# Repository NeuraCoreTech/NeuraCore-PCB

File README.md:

# FPGA Dev Board - Xilinx XC7Z020

Custom Zynq-7000 FPGA + ARM SoC development board based on the Xilinx XC7Z020-1CLG484I.

This repository contains the PCB design files, schematics, BOM, and hardware documentation for the board.

---

## Overview

This board is designed as a general-purpose Zynq development platform featuring:

- Xilinx XC7Z020 SoC
- DDR3L memory subsystem
- Gigabit Ethernet
- USB programming and UART interface
- USB OTG support
- QSPI boot flash
- Multi-rail power architecture
- FPGA PL expansion banks

The design targets embedded Linux, FPGA acceleration, digital design experimentation, and hardware/software co-design workflows.

---

## Hardware Features

### Processing System
- Xilinx XC7Z020-1CLG484I
- Dual-core ARM Cortex-A9
- FPGA programmable logic fabric

### Memory
- DDR3L memory interface
- Fly-by routed DDR topology
- Dedicated VTT termination rail

### Power Architecture
Power rails:
- 5V Input
- 3.3V
- 1.8V
- 1.35V
- 1.0V
- 0.675V DDR termination

Power sequencing implemented using:
- TPS56628 buck converters
- Dedicated PG sequencing
- Protection and filtering stages

### Connectivity
- Gigabit Ethernet (RTL8211F PHY)
- USB-C programming interface
- USB OTG via USB3320 ULPI PHY
- FT2232H for JTAG + UART

### Boot & Programming
- QSPI flash boot support
- Boot mode DIP switches
- Digilent HS3 compatible JTAG header

### FPGA I/O
- PL banks exposed for expansion
- HDMI-capable bank preparation
- Mixed-voltage IO support

---

## Repository Structure

```text
.
├── schematic/
├── pcb/
├── bom/
├── manufacturing/
├── images/
└── README.md
```

---

## Design Files

| File | Description |
|------|-------------|
| Schematic PDF | Complete board schematic |
| BOM | Bill of materials |
| PCB Layout | Board routing and placement |
| Gerbers | Manufacturing outputs |

---

## Key Components

| Component | Part |
|-----------|------|
| SoC | XC7Z020-1CLG484I |
| DDR3L | MT41K256M16TW |
| Ethernet PHY | RTL8211F-CG |
| USB PHY | USB3320 |
| USB/JTAG Interface | FT2232HL |
| QSPI Flash | W25Q512JVEIQ |

---

## Development Status

Current revision:
- v0.07

Status:
- Hardware prototype
- Under validation/testing

Known improvements and future revisions are documented within the schematic notes.

---

## Toolchain

Designed using:
- EasyEDA

Firmware/software targets:
- Vivado
- Vitis
- PetaLinux

---

## Bring-Up Checklist

- [ ] Verify all power rails
- [ ] Validate power sequencing
- [ ] DDR memory calibration
- [ ] QSPI boot validation
- [ ] JTAG connectivity test
- [ ] Ethernet PHY validation
- [ ] USB OTG validation

---

## Manufacturing Notes

Before fabrication:
- Verify impedance-controlled traces
- Review DDR length matching
- Validate power plane integrity
- Confirm connector footprints
- Review DFM constraints

---

## Contributors

- Krishna H. Patil
- Mohit Singh 
- Prajwal
- Arnav Yadnopavit

---
## Acknowledgements

This part of project (PCB) is heavily based on the open-source Zynq-7000 FPGA development board work by rehsd.

Original reference project:
https://github.com/rehsd/FPGA

Additional documentation and development notes:
https://www.rehsdonline.com/

The hardware architecture, schematic structure, and several subsystem implementations were adapted from the original project and modified for NeuraCoreTech requirements.

We thank rehsd for openly publishing the design resources and documentation.

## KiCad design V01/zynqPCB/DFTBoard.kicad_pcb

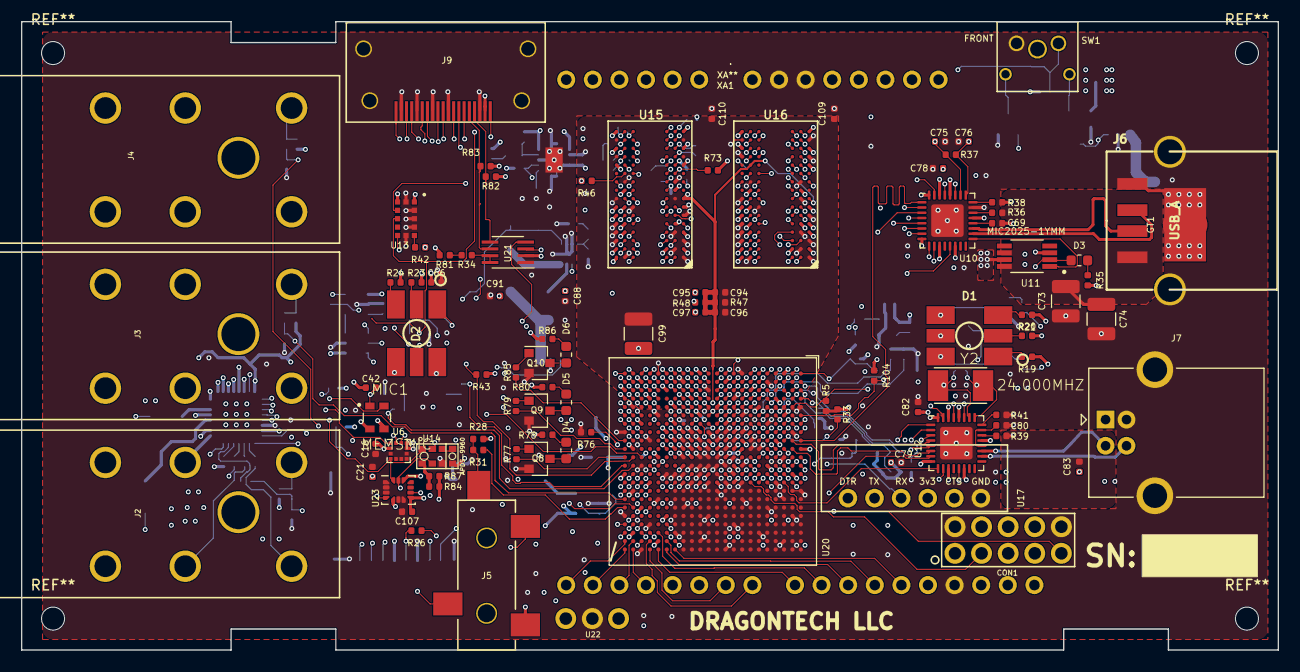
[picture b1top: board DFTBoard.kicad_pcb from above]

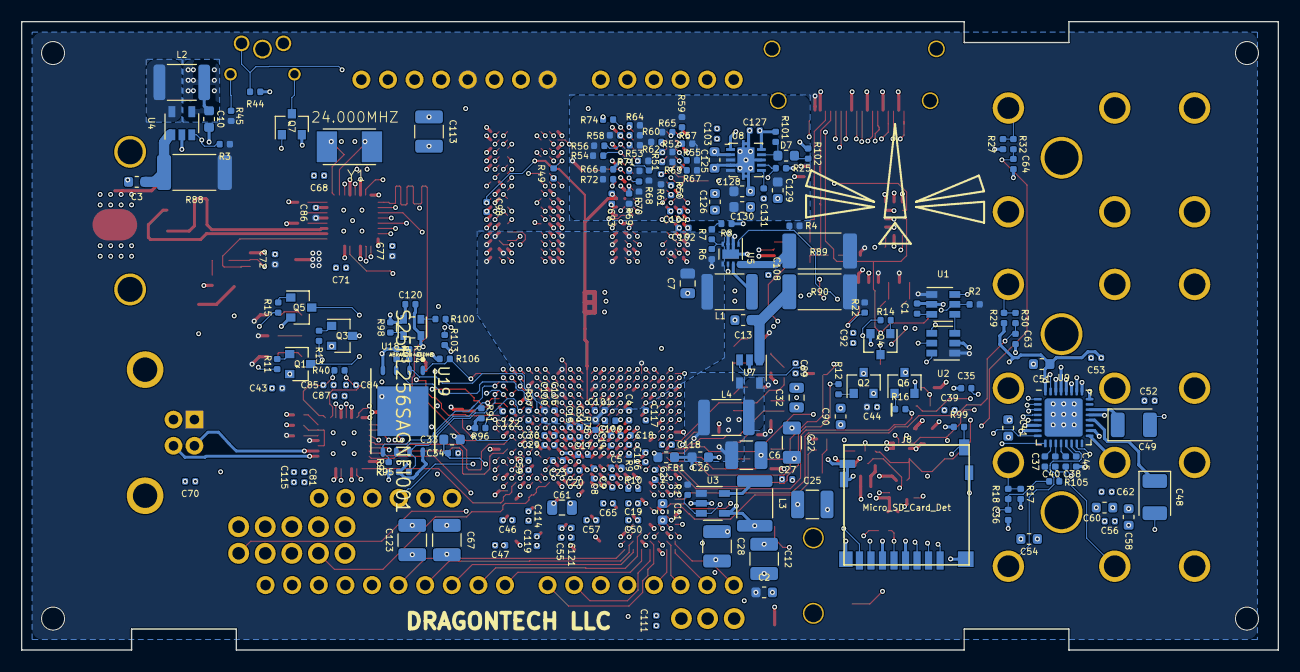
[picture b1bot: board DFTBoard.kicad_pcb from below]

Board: 8 copper layers, 120.0 x 60.0 mm, 295 parts (200 on the bottom side), 302 nets.

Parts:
C1, C4, C8, C14, C15, C17, C18, C23, C29, C30, C31, C34, C46, C47, C50, C55, C65, C78, C87, C101, C102, C103, C104, C108, C116, C117, C118, C119, C121: .47uF; C_0402_1005Metric
C2, C3, C10, C11, C13, C26, C33, C41, C51, C54, C58, C60, C90, C125, C126, C128, C129, C130: 10uF; C_0603_1608Metric
C5, C9, C19, C20, C21, C24, C27, C42, C57, C59, C66, C83, C89, C100, C114, C115, C122, C127: 4.7uF; C_0402_1005Metric
C6, C12, C25, C28, C67, C73, C74, C99, C123: 100uF; C_1210_3225Metric
C7, C32, C61: 47uF; C_0805_2012Metric
C16, C36, C39, C52, C53, C56, C62, C63, C64, C68, C70, C71, C72, C77, C79, C81, C82, C86, C88, C94, C95, C96, C97, C107, C131: .1uF; C_0402_1005Metric
C22: 330uF; C_1206_3216Metric
C35, C69, C80: 2.2uF; C_0402_1005Metric
C37, C38, C40, C43, C44, C45, C91, C92: 1uF; C_0402_1005Metric
C48, C49: 220uF Tant.; CP_EIA-3528-12_Kemet-T
C75, C76, C84, C85: 18pF; C_0402_1005Metric
C93, C98, C105, C106, C109, C110, C111, C120: .01uF; C_0402_1005Metric
C113: 47uF; C_1210_3225Metric
CON1: AVR-JTAG-10; XilinxJTAG
D1, D2: LED_RGB; PLCC6-SM-RGB-LED
D3, D4, D5, D6, D7: BLUE LED; C_0603_1608Metric
FB1: 120R, 100 MHz, size 0603; C_0603_1608Metric
GT1: GNDTIE; gndtie
J2, J3, J4: AUDIO JACK; RA49C14B
J5: JACK_TRS_4PINS; SJ-352X-SMT
J6: USB_A; USB-A-Receptacle-FCI_87583
J7: USB_B; USB_B_OST_USB-B1HSxx_Horizontal
J8: Micro_SD_Card_Det; AMPHENOL-114-00841-68
J9: HDMI_A; 10029449-111RLF
L1, L2, L3, L4: 2.2uH; C_1812_4532Metric
MIC1: MEMSMIC; MIC_SPW2430HR5H-B
Q1, Q2, Q3, Q4, Q5, Q6, Q7, Q8, Q9, Q10: IRLML2502; SOT-23
R1, R2, R3, R4, R5, R17, R27, R28, R29, R34, R81, R101: 100k; R_0402_1005Metric
R6, R33, R36, R39, R42, R43, R44: 10k; R_0402_1005Metric
R7, R46, R49: 240 1%; R_0402_1005Metric
R8, R9, R10, R74, R82, R83, R98, R103, R104: 4.7k; R_0402_1005Metric
R11, R12, R13, R14, R15, R16, R19, R20, R22, R23: 100; R_0402_1005Metric
R18, R30, R31, R32: 49.9k; R_0402_1005Metric
R21, R24, R35, R45, R78, R80, R86, R102: 150; R_0402_1005Metric
R25, R91, R92, R93, R94, R95, R96, R97, R106: 20k; R_0402_1005Metric
R26, R84, R87: 47; R_0402_1005Metric
R37, R40: 1M; R_0402_1005Metric
R38, R41: 8.06k 1%; R_0402_1005Metric
R47, R48: 10k 1%; R_0402_1005Metric
R50, R75, R76: 80.6 1%; R_0402_1005Metric
R51, R52, R53, R54, R55, R56, R57, R58, R59, R60, R61, R62, R63, R64, R65, R66, R67, R68, R69, R70, R71, R72, R73: 40.2 1%; R_0402_1005Metric
R77, R79, R85, R105: 1k; R_0402_1005Metric
R88, R89, R90: .05; R_2512_6332Metric
R99: 47k; R_0402_1005Metric
R100: 24.9 1%; R_0402_1005Metric
SW1: TL6215RF200BDT; tl6215_right_angle
U1, U2: LM3880; SOT-23-6
U3: SC189 - 1.0V; SOT-23-5
U4: SC189 - 3.3V; SOT-23-5
U5: TLV62080DSGx; WSON-8-1EP_2x2mm_P0.5mm_EP0.9x1.6mm
U6: LIS2HH12; LGA-12_2x2mm_P0.5mm
U7: SC189 - 1.8V; SOT-23-5
U8: TPS51200DRCR; VSON-10-1EP_3x3mm_P0.5mm_EP1.65x2.4mm_ThermalVias
U9: TLV320AIC3104; QFN-32-1EP_5x5mm_P0.5mm_EP3.65x3.65mm
U10, U12: USB3320; QFN-32-1EP_5x5mm_P0.5mm_EP3.1x3.1mm
U11: MIC2025-1YMM; SOP65P490X110-8N
U13: VL53L1CXV0FY/1; Optical_LGA12
U14: APDS-9960; APDS_9960
U15, U16: MT41K256M16HA-125_E; FBGA-96-DDR3-SDRAM
U17: FTDITypeUART; FTDI_CONN
U18: ABRACON-ASDMB; XTAL_ASDMB-24.000MHZ-LC-T
U19: S25FL256SAGNFI001; Cypress-002-18827-0-0-0
U20: xc7z020clg484; BGA-484_19.0x19.0mm_Layout22x22_P0.80mm_dia0.40mm
U21: PCA9306; SSOP-8_2.95x2.8mm_P0.65mm
U22: TSOP344; JUMPER_3PIN
U23: LSM6DSLTR; LGA-14_3x2.5mm_P0.5mm_LayoutBorder3x4y
XA1: Arduino_Uno_Shield_Simplified
Y1, Y2: 24.000MHZ; XTAL500X320X130N

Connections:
1v0en: R1.2, U1.6, U3.3
1v8en: R2.2, U1.5, U7.3
1v35PG: U5.6, U20.V4
1v35en: R4.2, U2.5, U5.1
3v3en: R3.2, U2.6, U4.3
+1V0: C8.1, C9.1, C11.1, C12.1, C23.1, C24.1, C25.1, C27.1, C28.1, C29.1, C30.1, C31.1, L3.2, U3.4, U20.G8, U20.H9, U20.H11, U20.J8, U20.J10, U20.J12, U20.J14, U20.K13, U20.L8, U20.L14, U20.M13, U20.N8, U20.N14, U20.P13, U20.R8, U20.R14
+1V8: C4.1, C5.1, C6.1, C14.1, C15.1, C17.1, C18.1, C19.1, C20.1, C22.1, C26.1, C32.1, C51.1, C53.1, C78.1, C87.1, CON1.4, FB1.2, L4.2, R9.2, R10.2, R17.1, R27.2, R28.2, R29.2, R44.1, U7.4, U9.32, U10.28, U10.30, U12.28, U12.30, U20.H10, U20.K9, U20.K11, U20.M9, U20.P9, U20.R12, U20.T7, U20.T8, U20.T9, U20.T10
+1V35: C7.1, C94.1, C96.1, C99.1, C100.1, C101.1, C102.1, C103.1, C104.1, C109.1, C110.1, C125.1, C126.1, L1.2, R6.2, R47.1, R75.2, U5.5, U8.2, U15.A1, U15.A8, U15.B2, U15.C1, U15.C9, U15.D2, U15.D9, U15.E9, U15.F1, U15.G7, U15.H2, U15.H9, U15.K2, U15.K8, U15.N1, U15.N9, U15.R1, U15.R9, U16.A1, U16.A8, U16.B2, U16.C1, U16.C9, U16.D2, U16.D9, U16.E9, U16.F1, U16.G7, U16.H2, U16.H9, U16.K2, U16.K8, U16.N1, U16.N9, U16.R1, U16.R9, U20.E2, U20.F5, U20.H1, U20.J4, U20.K7, U20.M3, U20.N6, U20.R2, U20.V1
+3V3: C10.1, C16.1, C21.1, C39.2, C41.2, C46.1, C47.1, C50.1, C52.2, C54.2, C55.1, C56.2, C57.1, C58.2, C59.1, C60.1, C61.1, C62.1, C65.1, C66.1, C67.1, C68.1, C70.1, C71.1, C79.1, C81.1, C82.1, C88.1, C89.1, C90.2, C91.2, C92.2, C107.1, C111.1, C113.1, C114.1, C115.1, C116.1, C117.1, C118.1, C119.1, C120.1, C121.1, C122.1, C123.1, C127.2, J8.4, L2.2, R5.1, R25.1, R33.2, R35.2, R42.1, R43.1, R82.1, R83.1, R84.2, R87.1, R95.2, R98.2, R99.1, R101.1, R102.2, R103.1, R104.1, R106.2, U4.4, U6.2, U6.9, U6.10, U8.10, U9.7, U9.18, U9.24, U9.25, U10.8, U10.11, U10.14, U10.32, U12.8, U12.11, U12.14, U12.32, U13.1, U13.11, U14.5, U17.3, U18.4, U19.8, U20.A10, U20.AA10, U20.AA20, U20.AB3, U20.AB13, U20.B3, U20.B13, U20.C6, U20.D9, U20.E12, U20.T5, U20.U8, U20.U18, U20.V11, U20.V21, U20.W4, U20.W14, U20.Y7, U20.Y17, U21.2, U22.3, U23.5, U23.8, U23.12, XA1.3V3, XA1.IORF
+5V: C2.1, C43.1, C44.1, C72.1, C77.1, C83.2, C86.1, J7.1, J9.18, R1.1, R2.1, R3.1, R4.1, R19.1, R20.1, R21.1, R22.1, R23.1, R24.1, R39.2, R45.1, R78.1, R80.2, R81.2, R86.2, R88.1, R89.1, R90.1, U1.1, U2.1, U3.1, U10.21, U11.7, U12.21, XA1.5V1, XA1.VIN
/Audio/HPRCOM_C_N: C48.2, J5.3
/Audio/HPRCOM_C_P: C49.2, J5.2
/Audio/HPSWITCH: J5.4, R28.1, R31.2
/Audio/INSWITCH: J2.TB, R17.2, R18.2
/Audio/JACK_INC_N: C40.1, U9.11
/Audio/JACK_INC_P: C37.1, U9.10
/Audio/JACK_IN_N: C40.2, J2.R
/Audio/JACK_IN_P: C37.2, J2.T
/Audio/LED_1BA: D1.3, R21.2
/Audio/LED_1BC: D1.4, Q5.3
/Audio/LED_1GA: D1.2, R20.2
/Audio/LED_1GC: D1.5, Q3.3
/Audio/LED_1RA: D1.1, R19.2
/Audio/LED_1RC: D1.6, Q1.3
/Audio/LED_2BA: D2.3, R24.2
/Audio/LED_2BC: D2.4, Q6.3
/Audio/LED_2GA: D2.2, R23.2
/Audio/LED_2GC: D2.5, Q4.3
/Audio/LED_2RA: D2.1, R22.2
/Audio/LED_2RC: D2.6, Q2.3
/Audio/LSWITCH: J3.TB, R29.1, R30.2
/Audio/MICBIAS: C35.2, C42.1, MIC1.1, U9.15
/Audio/RSWITCH: J4.TB, R27.1, R32.2
/Audio/SIGC_F: C38.2, MIC1.4
/Audio/SIG_F: C38.1, U9.12
/DDR3/PGOOD_LED: D7.2, R102.1
/DDR3/VREF: C93.1, C94.2, C95.1, C96.2, C97.1, C98.1, C105.1, C106.1, R47.2, R48.1, U8.1, U15.H1, U15.M8, U16.H1, U16.M8, U20.H7, U20.P7
/DDR3/ZQH: R46.1, U15.L8
/DDR3/ZQL: R49.1, U16.L8
/LCD50/SLED0_D: D4.1, Q8.3
/LCD50/SLED0_G: Q8.1, R77.1
/LCD50/SLED0_R: D4.2, R78.2
/LCD50/SLED1_D: D5.1, Q9.3
/LCD50/SLED1_G: Q9.1, R79.1
/LCD50/SLED1_R: D5.2, R80.1
/LCD50/SLED2_D: D6.1, Q10.3
/LCD50/SLED2_G: Q10.1, R85.1
/LCD50/SLED2_R: D6.2, R86.1
/Power/1V0TOLX: L3.1, U3.5
/Power/1V8TOLX: L4.1, U7.5
/Power/1V8_CS: C13.1, R90.2, U7.1
/Power/1V35_CS: C108.1, R89.2, U5.8
/Power/3V3TOLX: L2.1, U4.5
/Power/3V3_CS: C3.1, R88.2, U4.1
/Power/VCCAUX: C33.1, C34.1, FB1.1, U20.L10, U20.N10, U20.P11, U20.R10
/Sensors/3.3V_R: R84.1, R87.2, U14.8
/Sensors/TEMPO_LED_D: Q7.3, SW1.3
/Sensors/TEMPO_LED_R: R45.2, SW1.4
/USB/USBH_FLAG_LED: D3.2, R35.1
ACC_INT1: U6.12, U20.W12
ACC_INT2: U6.11, U20.V12
AX_TCLK: CON1.1, U20.G11
AX_TDI: CON1.9, U20.H13
AX_TDO: CON1.3, U20.G14
AX_TMS: CON1.5, U20.G12
BOOTSPI_CS: R106.1, U19.1, U20.A1
BOOTSPI_DQ0_BMODE3: R92.1, U19.5, U20.A2
BOOTSPI_DQ1_BMODE1: R94.1, U19.2, U20.F6
BOOTSPI_DQ2_BMODE2: R93.1, U19.3, U20.E4
BOOTSPI_DQ3_BMODE0: R95.1, U19.7, U20.A3
BOOTSPI_SCK_BMODE4: R91.1, U19.6, U20.A4
CLK33.33: R100.2, U18.3
DDR3_A0: R51.1, U15.N3, U16.N3, U20.M4
DDR3_A1: R52.1, U15.P7, U16.P7, U20.M5
DDR3_A2: R53.1, U15.P3, U16.P3, U20.K4
DDR3_A3: R54.1, U15.N2, U16.N2, U20.L4
DDR3_A4: R55.1, U15.P8, U16.P8, U20.K6
DDR3_A5: R56.1, U15.P2, U16.P2, U20.K5
DDR3_A6: R57.1, U15.R8, U16.R8, U20.J7
DDR3_A7: R58.1, U15.R2, U16.R2, U20.J6
DDR3_A8: R59.1, U15.T8, U16.T8, U20.J5
DDR3_A9: R60.1, U15.R3, U16.R3, U20.H5
DDR3_A10: R61.1, U15.L7, U16.L7, U20.J3
DDR3_A11: R62.1, U15.R7, U16.R7, U20.G5
DDR3_A12: R63.1, U15.N7, U16.N7, U20.H4
DDR3_A13: R64.1, U15.T3, U16.T3, U20.F4
DDR3_A14: R65.1, U15.T7, U16.T7, U20.G4
DDR3_BA0: R66.1, U15.M2, U16.M2, U20.L7
DDR3_BA1: R67.1, U15.N8, U16.N8, U20.L6
DDR3_BA2: R68.1, U15.M3, U16.M3, U20.M6
DDR3_CAS#: R70.1, U15.K3, U16.K3, U20.P3
DDR3_CKE: U15.K9, U16.K9, U20.V3
DDR3_CK_N: R50.2, U15.K7, U16.K7, U20.N5
DDR3_CK_P: R50.1, U15.J7, U16.J7, U20.N4
DDR3_CS#: R73.1, U15.L2, U16.L2, U20.P6
DDR3_DM0: U16.E7, U20.B1
DDR3_DM1: U16.D3, U20.H3
DDR3_DM2: U15.E7, U20.P1
DDR3_DM3: U15.D3, U20.AA2
DDR3_DQ0: U16.E3, U20.C3
DDR3_DQ1: U16.F7, U20.F2
DDR3_DQ2: U16.F2, U20.B2
DDR3_DQ3: U16.F8, U20.F1
DDR3_DQ4: U16.H3, U20.E3
DDR3_DQ5: U16.H8, U20.E1
DDR3_DQ6: U16.G2, U20.D3
DDR3_DQ7: U16.H7, U20.D1
DDR3_DQ8: U16.D7, U20.L3
DDR3_DQ9: U16.C3, U20.L1
DDR3_DQ10: U16.C8, U20.L2
DDR3_DQ11: U16.C2, U20.J1
DDR3_DQ12: U16.A7, U20.K1
DDR3_DQ13: U16.A2, U20.G2
DDR3_DQ14: U16.B8, U20.K3
DDR3_DQ15: U16.A3, U20.G1
DDR3_DQ16: U15.E3, U20.T3
DDR3_DQ17: U15.F7, U20.T1
DDR3_DQ18: U15.F2, U20.M1
DDR3_DQ19: U15.F8, U20.T2
DDR3_DQ20: U15.H3, U20.M2
DDR3_DQ21: U15.H8, U20.R1
DDR3_DQ22: U15.G2, U20.N3
DDR3_DQ23: U15.H7, U20.R3
DDR3_DQ24: U15.D7, U20.AA3
DDR3_DQ25: U15.C3, U20.Y1
DDR3_DQ26: U15.C8, U20.Y3
DDR3_DQ27: U15.C2, U20.W1
DDR3_DQ28: U15.A7, U20.AA1
DDR3_DQ29: U15.A2, U20.U1
DDR3_DQ30: U15.B8, U20.W3
DDR3_DQ31: U15.A3, U20.U2
DDR3_DQS0_N: U16.G3, U20.D2
DDR3_DQS0_P: U16.F3, U20.C2
DDR3_DQS1_N: U16.B7, U20.J2
DDR3_DQS1_P: U16.C7, U20.H2
DDR3_DQS2_N: U15.G3, U20.P2
DDR3_DQS2_P: U15.F3, U20.N2
DDR3_DQS3_N: U15.B7, U20.W2
DDR3_DQS3_P: U15.C7, U20.V2
DDR3_DRST#: R74.1, U15.T2, U16.T2, U20.F3
DDR3_ODT: R72.1, U15.K1, U16.K1, U20.P5
DDR3_RAS#: R69.1, U15.J3, U16.J3, U20.R5
DDR3_VTT: C128.1, C129.1, C130.1, R51.2, R52.2, R53.2, R54.2, R55.2, R56.2, R57.2, R58.2, R59.2, R60.2, R61.2, R62.2, R63.2, R64.2, R65.2, R66.2, R67.2, R68.2, R69.2, R70.2, R71.2, R72.2, R73.2, U8.3, U8.5
DDR3_VTT_EN: R25.2, U8.7, U20.B6
DDR3_WE#: R71.1, U15.L3, U16.L3, U20.R4
GND: C1.2, C2.2, C3.2, C4.2, C5.2, C6.2, C7.2, C8.2, C9.2, C10.2, C11.2, C12.2, C13.2, C14.2, C15.2, C16.2, C17.2, C18.2, C19.2, C20.2, C21.2, C22.2, C23.2, C24.2, C25.2, C26.2, C27.2, C28.2, C29.2, C30.2, C31.2, C32.2, C33.2, C34.2, C36.1, C39.1, C41.1, C43.2, C44.2, C46.2, C47.2, C50.2, C51.2, C53.2, C55.2, C57.2, C59.2, C61.2, C63.2, C64.2, C65.2, C66.2, C67.2, C68.2, C69.1, C70.2, C71.2, C72.2, C73.1, C74.1, C75.1, C76.1, C77.2, C78.2, C79.2, C80.1, C81.2, C82.2, C83.1, C84.1, C85.1, C86.2, C87.2, C88.2, C89.2, C90.1, C91.1, C92.1, C93.2, C95.2, C97.2, C98.2, C99.2, C100.2, C101.2, C102.2, C103.2, C104.2, C105.2, C106.2, C107.2, C108.2, C109.2, C110.2, C111.2, C113.2, C114.2, C115.2, C116.2, C117.2, C118.2, C119.2, C120.2, C121.2, C122.2, C123.2, C125.2, C126.2, C127.1, C128.2, C129.2, C130.2, C131.2, CON1.2, CON1.10, GT1.1, J6.4, J6.5, J7.4, J7.5, J8.6, J8.10, J8.11, J9.2, J9.5, J9.8, J9.11, J9.17, J9.SH, Q1.2, Q2.2, Q3.2, Q4.2, Q5.2, Q6.2, Q7.2, Q8.2, Q9.2, Q10.2, R8.2, R38.2, R41.2, R46.2, R48.2, R49.2, R74.2, R76.2, R91.2, R92.2, R93.2, R94.2, R96.2, R97.2, SW1.1, U1.2, U2.2, U3.2, U4.2, U5.2, U5.3, U5.9, U6.3, U6.5, U6.6, U6.7, U6.8, U7.2, U8.4, U8.8, U8.11, U9.6, U10.23, U10.33, U11.3, U12.33, U13.2, U13.3, U13.4, U13.6, U13.12, U14.6, U15.A9, U15.B1, U15.B3, U15.B9, U15.D1, U15.D8, U15.E1, U15.E2, U15.E8, U15.F9, U15.G1, U15.G8, U15.G9, U15.J2, U15.J8, U15.M1, U15.M9, U15.P1, U15.P9, U15.T1, U15.T9, U16.A9, U16.B1, U16.B3, U16.B9, U16.D1, U16.D8, U16.E1, U16.E2, U16.E8, U16.F9, U16.G1, U16.G8, U16.G9, U16.J2, U16.J8, U16.M1, U16.M9, U16.P1, U16.P9, U16.T1, U16.T9, U17.1, U18.2, U19.4, U19.9, U20.A5, U20.A15, U20.A16, U20.A17, U20.A18, U20.A19, U20.A20, U20.A21, U20.A22, U20.AA5, U20.AA15, U20.AB8, U20.AB18, U20.B8, U20.B15, U20.B16, U20.B17, U20.B18, U20.B19, U20.B20, U20.B21, U20.B22, U20.C1, U20.C11, U20.C15, U20.C16, U20.C17, U20.C18, U20.C19, U20.C20, U20.C21, U20.C22, U20.D4, U20.D14, U20.D15, U20.D16, U20.D17, U20.D18, U20.D19, U20.D20, U20.D21, U20.D22, U20.E7, U20.E15, U20.E16, U20.E17, U20.E18, U20.E19, U20.E20, U20.E21, U20.E22, U20.F10, U20.F15, U20.F16, U20.F17, U20.F18, U20.F19, U20.F20, U20.F21, U20.F22, U20.G3, U20.G9, U20.G10, U20.G15, U20.G16, U20.G17, U20.G18, U20.G19, U20.G20, U20.G21, U20.G22, U20.H6, U20.H8, U20.H12, U20.H14, U20.H15, U20.H16, U20.H17, U20.H18, U20.H19, U20.H20, U20.H21, U20.H22, U20.J9, U20.J11, U20.J13, U20.J15, U20.J16, U20.J17, U20.J18, U20.J19, U20.J20, U20.J21, U20.J22, U20.K2, U20.K8, U20.K10, U20.K12, U20.K14, U20.K15, U20.K16, U20.K17, U20.K18, U20.K19, U20.K20, U20.K21, U20.K22, U20.L5, U20.L9, U20.L11, U20.L12, U20.L13, U20.L15, U20.L16, U20.L17, U20.L18, U20.L19, U20.L20, U20.L21, U20.L22, U20.M8, U20.M10, U20.M11, U20.M12, U20.M14, U20.M15, U20.M16, U20.M17, U20.M18, U20.M19, U20.M20, U20.M21, U20.M22, U20.N1, U20.N9, U20.N11, U20.N12, U20.N13, U20.N15, U20.N16, U20.N17, U20.N18, U20.N19, U20.N20, U20.N21, U20.N22, U20.P4, U20.P8, U20.P10, U20.P12, U20.P14, U20.P15, U20.P16, U20.P17, U20.P18, U20.P19, U20.P20, U20.P21, U20.P22, U20.R9, U20.R11, U20.R13, U20.R15, U20.R16, U20.R17, U20.R18, U20.R19, U20.R20, U20.R21, U20.R22, U20.T13, U20.T15, U20.T16, U20.T17, U20.T18, U20.T19, U20.T20, U20.U3, U20.U13, U20.V6, U20.V16, U20.W9, U20.W19, U20.Y2, U20.Y12, U20.Y22, U21.1, U22.2, U23.1, U23.2, U23.3, U23.6, U23.7, XA1.GND1, XA1.GND2, XA1.GND3
GNDA: C35.1, C42.2, C45.1, C52.1, C54.1, C56.1, C58.1, C60.2, C62.2, GT1.2, J2.RB, J2.S, J3.RB, J3.S, J4.RB, J4.S, J5.1, MIC1.2, MIC1.3, U9.17, U9.21, U9.26, U9.33
HDMI_B_N: J9.3, U20.AA8
HDMI_B_P: J9.1, U20.AA9
HDMI_CEC: J9.13, U20.W5
HDMI_CLK_N: J9.12, U20.Y8
HDMI_CLK_P: J9.10, U20.Y9
HDMI_G_N: J9.6, U20.AA6
HDMI_G_P: J9.4, U20.AA7
HDMI_HEAC_N: J9.19, U20.AB6
HDMI_HEAC_P: J9.14, U20.AB7
HDMI_R_N: J9.9, U20.Y5
HDMI_R_P: J9.7, U20.Y6
HPCOM_N: C48.1, U9.20
HPCOM_P: C49.1, U9.22
I2C5_HDMI_SCLK: J9.15, R83.2, U21.6
I2C5_HDMI_SDA: J9.16, R82.2, U21.5
I2C33_HDMI_SCLK: U20.U9, U21.3
I2C33_HDMI_SDA: U20.U10, U21.4
I2C33_SCLK: R103.2, U6.1, U9.8, U13.10, U14.7, U20.C5, U23.13
I2C33_SDA: R104.2, U6.4, U9.9, U13.9, U14.1, U20.A6, U23.14
I2S_ADCSD: U9.5, U20.AB15
I2S_BCLK: U9.2, U20.AA13
I2S_DACSD: U9.4, U20.AA14
I2S_LRCLK: U9.3, U20.AB14
I2S_MCLK: U9.1, U20.Y13
IMU_INT1: U20.W15, U23.4
IMU_INT2: U20.Y15, U23.9
INIT_B: R10.1, U20.T14
IR_RX: U20.AA18, U22.1
JD_HOUT: R31.1, U20.AB17
JD_IN: C36.2, R18.1, R105.2, U20.W17
JD_LOUT: C63.1, R30.1, U20.AB16
JD_ROUT: C64.1, R32.1, U20.AB19
LCD_D0: U20.AB21, XA1.D0
LCD_D1: U20.AB22, XA1.D1
LCD_D2: U20.U19, XA1.SCL
LCD_D3: U20.W20, XA1.SDA
LCD_D4: U20.V5, XA1.A5
LCD_D5: U20.AB5, XA1.A4
LCD_D6: U20.AB4, XA1.A3
LCD_D7: U20.AA4, XA1.A2
LCD_D8: U20.Y4, XA1.A1
LCD_D9: U20.AB2, XA1.A0
LCD_D10: U20.U20, XA1.AREF
LCD_D11: U20.AA21, XA1.D2
LCD_D12: U20.AA22, XA1.D3
LCD_D13: U20.Y21, XA1.D4
LCD_D14: U20.Y20, XA1.D5
LCD_D15: U20.W22, XA1.D6
LCD_D16: U20.W21, XA1.D7
LCD_D17: U20.V22, XA1.D8
LCD_D18: U20.V20, XA1.D9
LCD_D19: U20.U22, XA1.D10
LCD_D20: U20.U21, XA1.D11
LCD_D21: U20.T22, XA1.D12
LCD_D22: U20.T21, XA1.D13
LCD_D23: U20.AB1, XA1.RST1
LED_1B_CTRL: R15.2, U20.Y19
LED_1G_CTRL: R13.2, U20.AB20
LED_1R_CTRL: R11.2, U20.AA19
LED_2B_CTRL: R16.2, U20.AA12
LED_2G_CTRL: R14.2, U20.Y11
LED_2R_CTRL: R12.2, U20.AB12
LOUT_N: J3.R, U9.28
LOUT_P: J3.T, U9.27
unnamed: C1.1, U1.3
unnamed: C45.2, U9.13
unnamed: C69.2, U10.20
unnamed: C75.2, R37.1, U10.26, Y1.1
unnamed: C76.2, R37.2, U10.25, Y1.2
unnamed: C80.2, U12.20, U12.23
unnamed: C84.2, R40.1, U12.26, Y2.1
unnamed: C85.2, R40.2, U12.25, Y2.2
unnamed: C131.1, U8.6
unnamed: D7.1, R101.2, U8.9
unnamed: L1.1, U5.7
unnamed: Q1.1, R11.1
unnamed: Q2.1, R12.1
unnamed: Q3.1, R13.1
unnamed: Q4.1, R14.1
unnamed: Q5.1, R15.1
unnamed: Q6.1, R16.1
unnamed: R6.1, R7.1, U5.4
unnamed: R7.2, R8.1
unnamed: R26.1, U20.D6
unnamed: R33.1, U20.C9
unnamed: R34.1, U21.7, U21.8
unnamed: R34.2, R81.1
unnamed: R36.1, U10.22
unnamed: R38.1, U10.24
unnamed: R39.1, U12.22
unnamed: R41.1, U12.24
unnamed: R42.2, U13.5
unnamed: R75.1, U20.M7
unnamed: R76.1, U20.N7
unnamed: R98.1, U18.1
unnamed: R100.1, U20.F7
unnamed: R105.1, U9.14
unnamed: U1.4, U2.3
unnamed: U14.3, U14.4
PROGRAM_B: R9.1, U20.T11
RF2_IRQ: U14.2, U20.E6
RF_IRQ: R43.2, U13.7, U20.AA11
ROUT_N: J4.R, U9.30
ROUT_P: J4.T, U9.29
SD_CD: J8.9, R99.2, U20.A13
SD_CLK: J8.5, R26.2
SD_CMD: J8.3, U20.E9
SD_D0: J8.7, U20.A7
SD_D1: J8.8, U20.E10
SD_D2: J8.1, U20.A8
SD_D3: J8.2, U20.F11
STATLED_0: R77.2, U20.AB11
STATLED_1: R79.2, U20.AB10
STATLED_2: R85.2, U20.AB9
TEMPO_LED: Q7.1, U20.R6
TEMPO_SW: R44.2, SW1.2, U20.Y14
TLV_RST#: U9.31, U20.AA17
UART33_RX: U17.4, U20.G7
UART33_TX: U17.5, U20.B4
USB0_CLK: U10.1, U20.A9
USB0_D0: U10.3, U20.C7
USB0_D1: U10.4, U20.G13
USB0_D2: U10.5, U20.B12
USB0_D3: U10.6, U20.F14
USB0_D4: U10.7, U20.A12
USB0_D5: U10.9, U20.B14
USB0_D6: U10.10, U20.F13
USB0_D7: U10.13, U20.C13
USB0_RST: U10.27, U20.D10
USB0_dir: U10.31, U20.E8
USB0_nxt: U10.2, U20.F9
USB0_stp: U10.29, U20.A11
USB1_CLK: U12.1, U20.D11
USB1_D0: U12.3, U20.E13
USB1_D1: U12.4, U20.B9
USB1_D2: U12.5, U20.D12
USB1_D3: U12.6, U20.B10
USB1_D4: U12.7, U20.E14
USB1_D5: U12.9, U20.C14
USB1_D6: U12.10, U20.D13
USB1_D7: U12.13, U20.C10
USB1_RST: U12.27, U20.C12
USB1_dir: U12.31, U20.C8
USB1_nxt: U12.2, U20.B11
USB1_stp: U12.29, U20.D8
USBD_D_N: J7.2, U12.19
USBD_D_P: J7.3, U12.18
USBH_CPEN: U10.17, U11.1
USBH_D_N: J6.2, U10.19
USBH_D_P: J6.3, U10.18
USBH_FAULT: D3.1, U11.2, U20.B7
USBH_VBUS: C73.2, C74.2, J6.1, R36.2, U11.6, U11.8
VMODE0: R96.1, U20.D5
VMODE1: R97.1, U20.E5
ZYNQ_POR: R5.2, U2.4, U20.B5

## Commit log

2026-02-23 import pcb design
2026-02-25 Updated Audio schematic
2026-02-25 Remove Sensors
2026-02-25 Audio update
2026-02-25 Update audio schematic
2026-05-10 Prettify and added the final and new pcb
2026-05-10 Update acknowledgements in README.md
    Expanded acknowledgements section to include additional references and contributions.
2026-05-13 updated bom
2026-05-24 Fix formatting of contributors list in README
2026-06-27 final
